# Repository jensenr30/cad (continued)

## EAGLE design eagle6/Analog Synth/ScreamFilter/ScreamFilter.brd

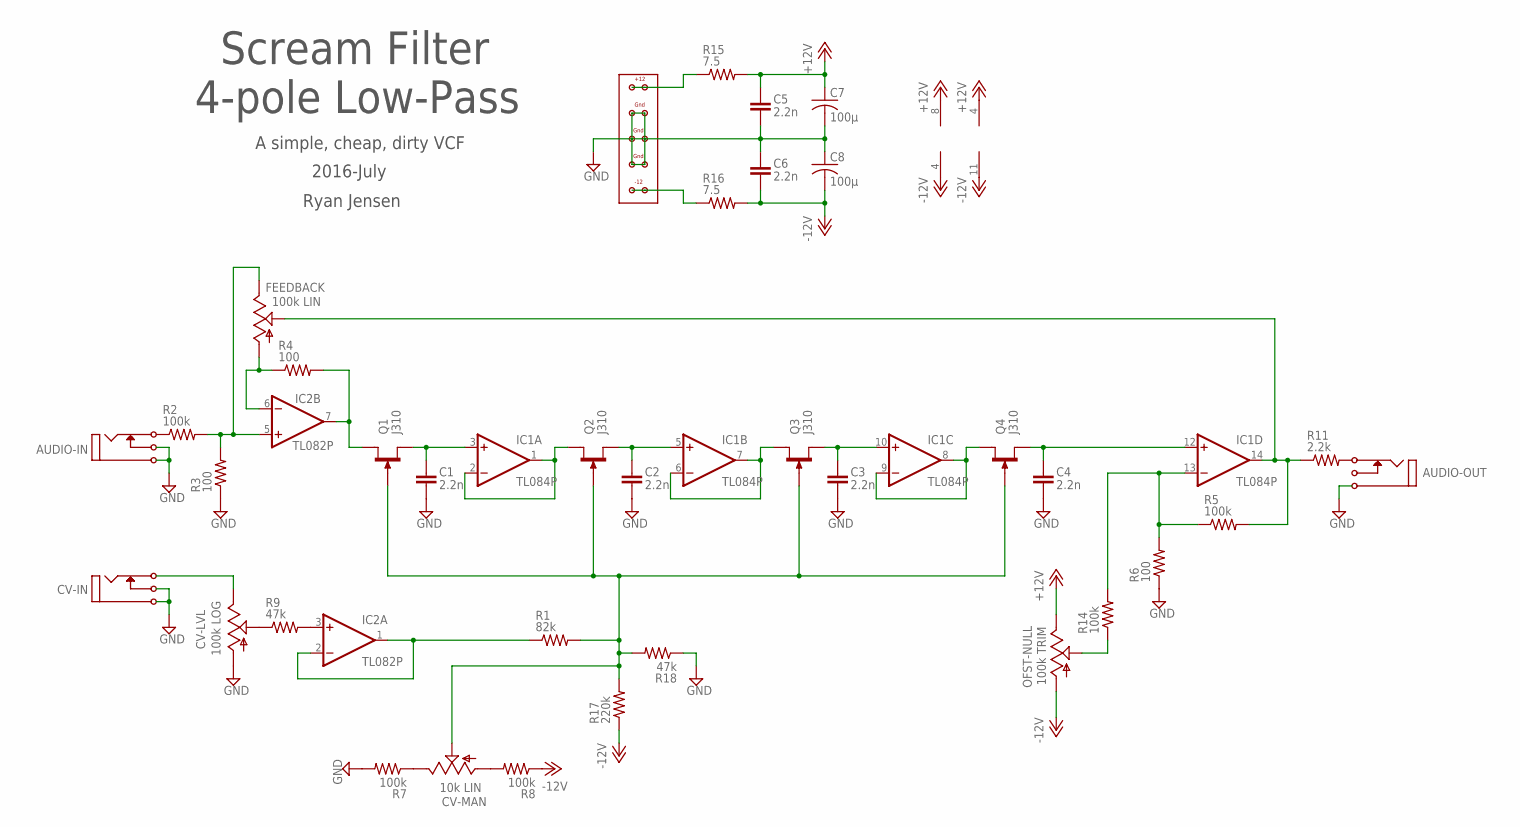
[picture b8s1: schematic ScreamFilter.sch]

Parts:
AUDIO-IN: I/O; MONO_JACK
AUDIO-OUT: I/O; MONO_JACK
C1, C2, C3, C4, C5, C6: 2.2n; C025-025X050
C7, C8: 100µ; C025-050X050
CV-IN: I/O; MONO_JACK
CV-LVL: 100k LOG; B64Y
CV-MAN: 10k LIN; B64Y
FEEDBACK: 100k LIN; B64Y
IC1: TL084P; DIL14
IC2: TL082P; DIL08
OFST-NULL: 100k TRIM; B64Y
Q1, Q2, Q3, Q4: J310; TO92R
R1: 82k; 0204/7
R2, R5, R7, R8, R14: 100k; 0204/7
R3, R4, R6: 100; 0204/7
R9, R18: 47k; 0204/7
R11: 2.2k; 0204/7
R15, R16: 7.5; 0204/7
R17: 220k; 0204/7
U$1: EURORACK-POWER

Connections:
+12V: C5.1, C7.1, IC1.4 (V+), IC2.8 (V+), OFST-NULL.E, R15.2
-12V: C6.2, C8.2, IC1.11 (V-), IC2.4 (V-), OFST-NULL.A, R8.1, R16.2, R17.1
GND: AUDIO-IN.P$1, AUDIO-IN.P$3 (P3), AUDIO-OUT.P$1, C1.2, C2.2, C3.2, C4.2, C5.2, C6.1, C7.2, C8.1, CV-IN.P$1, CV-IN.P$3 (P3), CV-LVL.A, R3.1, R6.1, R7.2, R18.1, U$1.P$3, U$1.P$4, U$1.P$5, U$1.P$6, U$1.P$7, U$1.P$8
unnamed: AUDIO-IN.P$2 (P2), R2.1
unnamed: FEEDBACK.E, IC2.5 (+IN), R2.2, R3.2
unnamed: IC2.7 (OUT), Q1.D, R4.2
unnamed: C1.1, IC1.3 (+IN), Q1.S
unnamed: IC1.1 (OUT), IC1.2 (-IN), Q2.D
unnamed: C2.1, IC1.5 (+IN), Q2.S
unnamed: IC1.6 (-IN), IC1.7 (OUT), Q3.D
unnamed: FEEDBACK.S, IC1.14 (OUT), R5.2, R11.1
unnamed: C3.1, IC1.10 (+IN), Q3.S
unnamed: IC1.8 (OUT), IC1.9 (-IN), Q4.D
unnamed: C4.1, IC1.12 (+IN), Q4.S
unnamed: CV-MAN.E, R7.1
unnamed: OFST-NULL.S, R14.1
unnamed: IC1.13 (-IN), R5.1, R6.2, R14.2
unnamed: CV-MAN.A, R8.2
unnamed: CV-IN.P$2 (P2), CV-LVL.E
unnamed: IC2.3 (+IN), R9.2
unnamed: CV-MAN.S, Q1.G, Q2.G, Q3.G, Q4.G, R1.2, R17.2, R18.2
unnamed: AUDIO-OUT.P$2 (P2), R11.2
unnamed: CV-LVL.S, R9.1
unnamed: FEEDBACK.A, IC2.6 (-IN), R4.1
unnamed: R16.1, U$1.P$9, U$1.P$10
unnamed: R15.1, U$1.P$1, U$1.P$2
unnamed: IC2.1 (OUT), IC2.2 (-IN), R1.1

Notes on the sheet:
Scream Filter 4-pole Low-Pass
A simple, cheap, dirty VCF
Ryan Jensen
2016-July

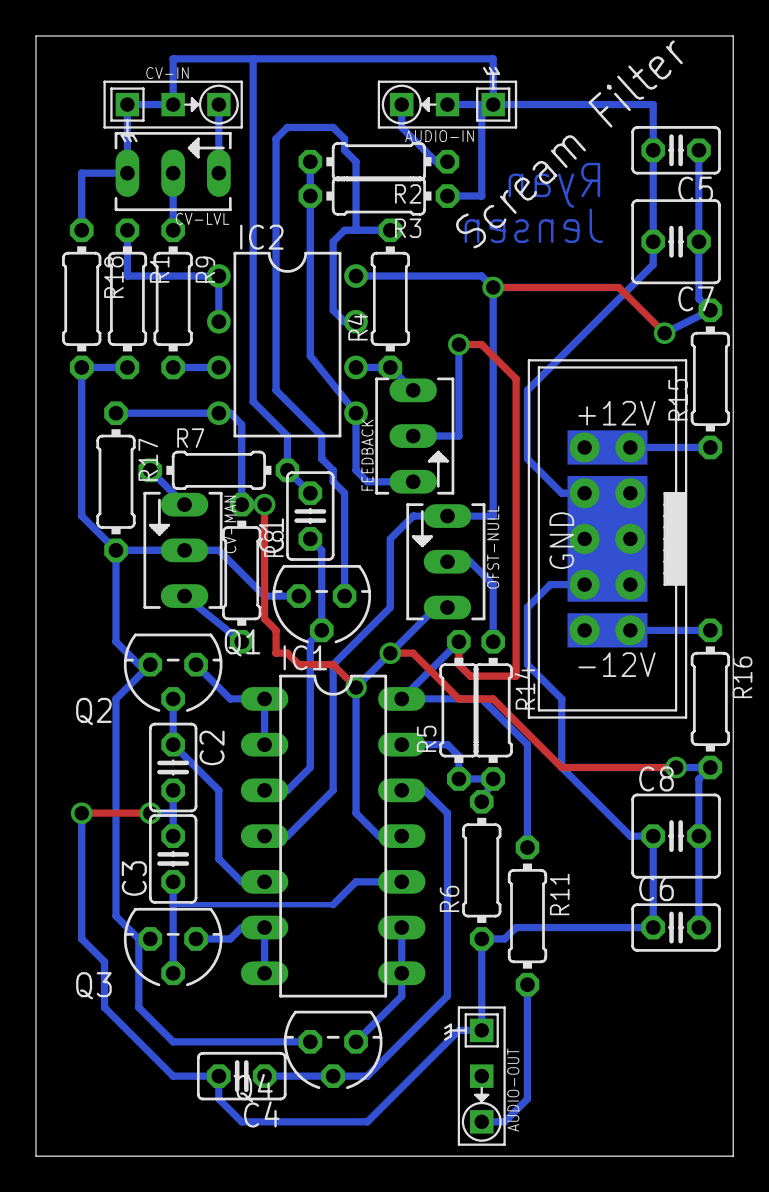
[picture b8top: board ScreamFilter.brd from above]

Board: 2 copper layers, 38.7 x 62.2 mm, 37 parts (0 on the bottom side), 27 nets.

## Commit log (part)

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2014-10-26 added pre-existing eagle schematics and libraries.
2014-11-16 Worked on the triangle wave part of the analog VCO.
2014-11-28 Working on analog synth stuff. Also just started the schematic for senior design (really just making the ATtiny24A symbol and package)
2015-01-23 added pad-per-hole strip protoype board, updated VCO v1, did some gerber stuff
2015-01-24 integrating EAGLE-6.6.0 stuff
2015-01-25 working on VCO-v1. optimizing circuit. removing resistors in favor of better pot placement.
2015-01-26 added reset circuitry to VCO-v1
2015-01-26 fixed capacitor values
2015-01-26 improved formatting of triangle->sine converter page (7)
2015-01-27 fixed stupid error with op amp inputs for frequency generation.
2015-01-31 fixed Reset LED configuration
2015-02-05 VCO-v1 had SOMETHING done to it. What was done, I know not.
2015-02-09 creating AR board (Attack/Release)
2015-02-15 added Attack-Release schematic with a JFET-based VCA that won't work. I will need to modify the schematic for a bual board.
2015-02-17 Added Voltage Controlled Amplifier v1. The thing actually works to some degree!!
2015-02-27 working on senior design circuit and pcb
2015-02-28 worked on the schematic
2015-03-04 working on VCA-v1
2015-03-04 Working on Power Distribution Board
2015-03-06 Working on VCA-v1 more. I need to add LED driving circuitry (LEDs, resistors, and a -5V source). Also, the silkscreen for the audio in/out jacks is on the back layer instead of the front. Fix this.
2015-03-07 working on VCA more. added caps to filter RF by shunting high frequencies to ground.
2015-03-07 "Finished" VCA-v1. Ordered PCBs from dirtypcbs.com.
2015-03-08 started schematic for analog switch. also changed a diode in a standard library
2015-03-09 revamped the analog switch circuit. two op amps, two transistors (a diode, and some resistors)
2015-03-13 Added a front panel for the Tri-Analog-Switch
2015-03-21 working on senior design and analog switch
2015-03-21 Updated the analog switch so that it doesn't suck so much. - Removed transistor and resistors. - Replaced with a diode to the gate of the JFET. - Changed grounding resistor from 330k to 56k. This was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
2015-03-23 working on VCA front panel.
    -CV at the top (with attenuation proceeded by offset adjustment)
    - Audio In in the middle (with attenuation)
    - Audio Out at the bottom.
2015-03-24 changed a single trace placement with the Senior Design project.(it was too close to the edge of the board) Also exported gerbers for OSHpark
2015-08-24 added a few things; rendered VCO-v1 pdf
2015-09-13 started echo chamber with eagle and kicad
2015-09-14 working on the Echo Chamber schematic; PT2399 was added to \!synth_sch library
2015-09-14 fixed little bug with the Echo Chamber schematic
2015-09-14 added some guide information to the schematic for the LEDs and the diodes, as well as referencing the data sheet as the source of the basic design of the PT2399 circuit
2015-09-20 I realized that I have more work to do on the schematic than I do have to do on the Panel. The circuit needs to be figured out exactly first. But that shouldn't take long. The filter may pose a sligh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
2015-10-10 working on VCO-v2 schematic; added a library part for CA3096 transistor array into that library that some other guy started
2015-10-10 VCO-v2 progress: linear voltage to exponential current converter and hysteresis circuit
2015-10-10 VCO-v2 high frequency compensation
2015-10-10 VCO-v2 - power supply. Also, I need to change those integration caps to be polarized types in the schematic and on the pcb...
2015-10-11 VCO-v2 PWM and Triangle outputs
2015-10-11 VCO-v2 PWM control voltage attenuation
2015-10-11 VCO-v2 Sine (from VCO-v1 basically)
2015-10-11 VCO-v2 LEDs sheet and signal names
2015-10-13 VCO-v2 - version 2.1 released! I changed a few things with the triangle-to-freq converter; I made the LEDs go into a bjt voltage source rather than the +5 V and -5 V regulated supplies, because conne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
2015-10-17 fixed error in VCO-v2 schematic - CV sum had a tuner going to -5 V instead of -9 V
2015-10-18 VCO-v2 - increased size of resistors around the triangle-wave x2 gain stage
2015-10-21 VCO-v2 improved readability
2015-10-24 VCO-v2.2 - updated an LED resistor value and exported PDF
2015-11-03 PS-VCO: created schematic
2015-11-03 PS-VCO creating PCB
2015-11-03 PS-VCO still working on PCB - making gerbers. proof reading. Need to add an LED for the CV signal
2015-11-03 PS-VCO added LED - organizing text on PCB
2015-11-06 Cigar Box Sequencer - created first draft of the front panel.
2015-11-08 CBS - Cigar Box Sequencer - 8 step - starting to put together a schematic for it
2015-11-08 CBS: moved file into folder
2015-11-09 CBS - still working on Cigar Box Sequencer schematic
2015-11-10 CBS - still working through Cigar Box Sequencer details
2015-11-14 CBS: working on skiimatic
2015-11-14 CBS: schematic (still)
2015-11-14 CBS: schematic (stillstill)
2015-11-14 CBS: chem and front panel of the cigar box
2015-11-14 CBS: added the switches for the GATE output that replaces the clock output
2015-11-15 CBS: updating schematic to make the GATE_OUT work properly
2015-11-15 CBS: generated pdf
2015-11-15 CBS: fixed output resistor values
2015-11-15 CBS: fixed output resistor values - other ones
2015-11-15 CBS: fixed output jack ground issue
2015-11-15 CBS: fixed the CV-OUT resistor value from 2.2k to 1k
2015-11-16 CBS: changed the binary input/output bypass connections so that the user cannot short the outputs of the 193 binary counter.
2015-11-16 CBS: added pdf documents
2015-11-26 added another prototype board type
2015-12-01 CBS: updating schematic and generating another pdf.
2015-12-01 CBS: fixed missing potentiometer value for output CV filter
2016-02-22 PS-VCO: updating documentation and schematic. rendered pdfs for schematic and pcb. generated a BOM
2016-02-25 updating PS-VCO. Changed a resistor value to get closer to 50% duty cycle. It is still very approximate, but before the duty cycle was around 25% or 30% or something really obviously not balanced.
2016-02-25 adding some data to the schematic
2016-02-26 updated a few PS-VCO things
2016-03-13 working on mixer; PS-VCO triple front panel
2016-03-19 working on Stroboscope
2016-03-19 stroboscope
2016-04-02 added a surface mount package to the ATtiny24A device
2016-04-23 FreqCount84 adding Input Stage (AC / DC coupling and Amplification); updated resistor and capacitor libraries so that the values and names are on the same side of the symbol rather than opposite sides
2016-04-25 added the FTDI USB->RS232 chip into the schematic because I am using it now.
2016-04-25 adding notes to FTDI RS232 chip.
2016-06-06 adding VCA-v2 initial stuff to the repo. SCH is not really created yet, I just copied VCA-v1
2016-06-07 created VCA-v2 schematic. PCB exists, but it is not layed out or routed
2016-06-11 added DMMT3904W to part library in synth_sch; making progress on VCA-v2 layout
2016-06-11 making progress on VCA-v2. Updated the Eurorack power connector
2016-06-11 making some progress on VCA-v2
2016-06-11 VCA-v2. Using eagle version 7.6 to generate the gerbers because my install of version 6 was having trouble finding its output devices... whatever that means...
2016-06-12 organizing VCA-v2 stuff; pdf
2016-06-12 updating text placement and generating the assembly drawings for computer reference and for printing
2016-06-18 making progress on a breakout board
2016-06-18 finished laying out the breakout board. going to order this soon.
2016-06-29 prototype board gerbers; ScreamFilter
2016-07-08 nothing
2016-07-11 VCA-v2 new schematic pdf; ScreamFilter layout has begun.
2016-07-13 working on ScreamFilter layout. close to finished
2016-07-15 working on ScreamFilter DIY layout
2017-07-06 added .gitignore
2017-07-06 updated .gitignore to include _autosave- files
2017-07-06 removing the autosave file in SRBOB
2017-07-06 updating SRBOB project
2017-07-06 minor modification to XPhone Input Board
2017-07-09 forgot to save XPhone/Input_Board project file
2017-07-14 ^XPhone Input Board layout; +bug record
2017-07-14 +pdf of schematic for XPhone/Input_Board
2017-07-14 XPhone/Input_Board components are roughly organized
2017-07-14 XPhone/Input_Board +power connectors
2017-07-15 XPhone/Input_Board
2017-07-15 made tl084 a SOIC and returned 74hc14 back to a DIP
2017-07-19 XPhone/Input_Board - placed parts around L3 amplifier
2017-07-19 XPhone/Input_Board - laid traces for parts around L3
2017-07-19 fixed -12V symbol (used to have +12V pin name which automatically connected it with the +12 V supply. BAD. Updated XPhone/Input_Board too
2017-07-19 XPhone/Input_Board touching-up first layout of amplifier circuit
2017-07-20 ignoring the modules I add
2017-07-20 updating transistor REF** in XPhone/Input_Board
2017-07-20 XPhone/Input_Board L4 circuit
2017-07-20 XPhone/Input_Board ^layout; using wide TO-92; close to done
2017-07-20 XPhone/Input_Board - just realized I forgot to add V_ENV_BIAS to the circuit; continuing layout...
2017-07-20 XPhone/Input_Board finished laying out everything of importance (except the V_ENV_BIAS\!
2017-07-20 XPhone/Input_Board removing unnecessary caps
2017-07-20 XPhone/Input_Board .pro file
2017-07-20 XPhone/Input_Board fixed L orientation (not a big deal, but it bugged me)
2017-07-22 XPhone/Input_Board +ENV_BIAS to circuit
2017-07-22 V_ENV_BIAS
2017-07-22 polishing the F.Fab layer
2017-07-22 working on silscreen
2017-07-22 XPhone TODO list
2017-07-24 XPhone/Input_Board +mounting holes; ^silkscreen; +bug picture
2017-07-25 XPhone/Input_Board ^PCB; +2x2 Panel
2017-07-25 fixed generation of panel
2017-07-25 initial panel gerbers - not ready yet
2017-07-26 XPhone/Input Board
2017-07-26 optimizing XPhone/Input Board layout for cutting it into pieces; traces routed not so close to the board
2017-07-26 creating panel and gerbers
2017-07-26 made a panel gerber package for dirtypcbs
2019-05-04 deleted: references, bugs, and Test_Project
2019-05-04 Preparing for merge with other CAD program files... <<{KiCad 4}>>
2019-05-04 PS-VCO, ScreamFilter, VCA-v2, and XPhone stuff. (something I must have done 2 years ago...)
2019-05-04 Preparing for merge with other CAD program files... <<{Eagle 6.6.0}>>
2019-05-04 setting up a README.md for CAD repo
2019-05-04 rendering PDFs of old schematics to ensure information is not difficult to access later on...; deleting some useless old projects.
2019-05-04 organizing eagle6/Synth folder - deleting some old junk...
2019-05-04 eagle6: renamed Sequencer -> 8-Note Sequencer; organizing misc files...
2019-05-04 eagle6: rendering old schematics...
2019-05-04 renamed: Strobeoscope -> Stroboscope
2019-05-04 README.md: changed "VU Meter" to "VU meter" (lowercase m)
    This is linux-type stuff, my man; the case of the letter matters.
2019-05-04 adding LTspice IV simulation files to the repo
2019-05-04 README.md: added section about LTspice IV
2019-05-04 + inverter XOR noise generator pics
2019-05-04 LTspice IV: adding a simple solenoid switching simulation
2019-08-12 + magnetoscope project (almost nothing - just an inductor on a blank schematic at this point)
2022-06-16 adding FreeCad and Silent Susan project
2022-06-16 adding kicad magnetoscope from 2 years ago
2022-06-17 silent susan v5.5 - fixed bolt hole; got Path looking good; generate first G-code; added G-code cheat sheet web page"
2022-06-18 created g-code for base
2022-06-19 changed washer clearance to 100 thou on each side to avoid interference.
2022-06-20 created silent susan v6 based on dad's design
2022-06-20 silent susan v6
2022-08-19 putting together spreadsheet for parameteric definition of napkin holder
2022-08-19 napkin holder v3 CAD and g-code
2022-08-21 created napkin holder v2.2
2022-08-26 fixed napkin holder 2.2
2023-03-26 cabinet side holes
2024-07-27 Created expression-pedal-to-pwm schematic
2024-07-29 Expression-Pedal-to-PWM - make schematic 8.5x11 in
2024-07-31 Layout components and traces for Expression Pedal PWM Motor Controller
2024-07-31 Add copper pour and via stitching to Expression-Pedal-to-PWM
2024-07-31 Export Rev 1 Expression Pedal to PWM
2024-08-20 Add fixed TerminalBlock_MetzConnect footprints
2024-08-20 Fix expression pedal Terminal Block
2025-10-11 Add wisconsin silhouette
